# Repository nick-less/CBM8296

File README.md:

The files I used to repair my Commodore 8296, maybe someone finds this useful. 
Its not my own work I just combined the XC9536 PLA from http://www.nightfallcrew.com/18/11/2009/xilink-cpld-xc9536-replacement-pla-for-commodore-64/
with the Equations from http://www.zimmers.net/anonftp/pub/cbm/firmware/computers/pet/8296/index.html

This is how it looks

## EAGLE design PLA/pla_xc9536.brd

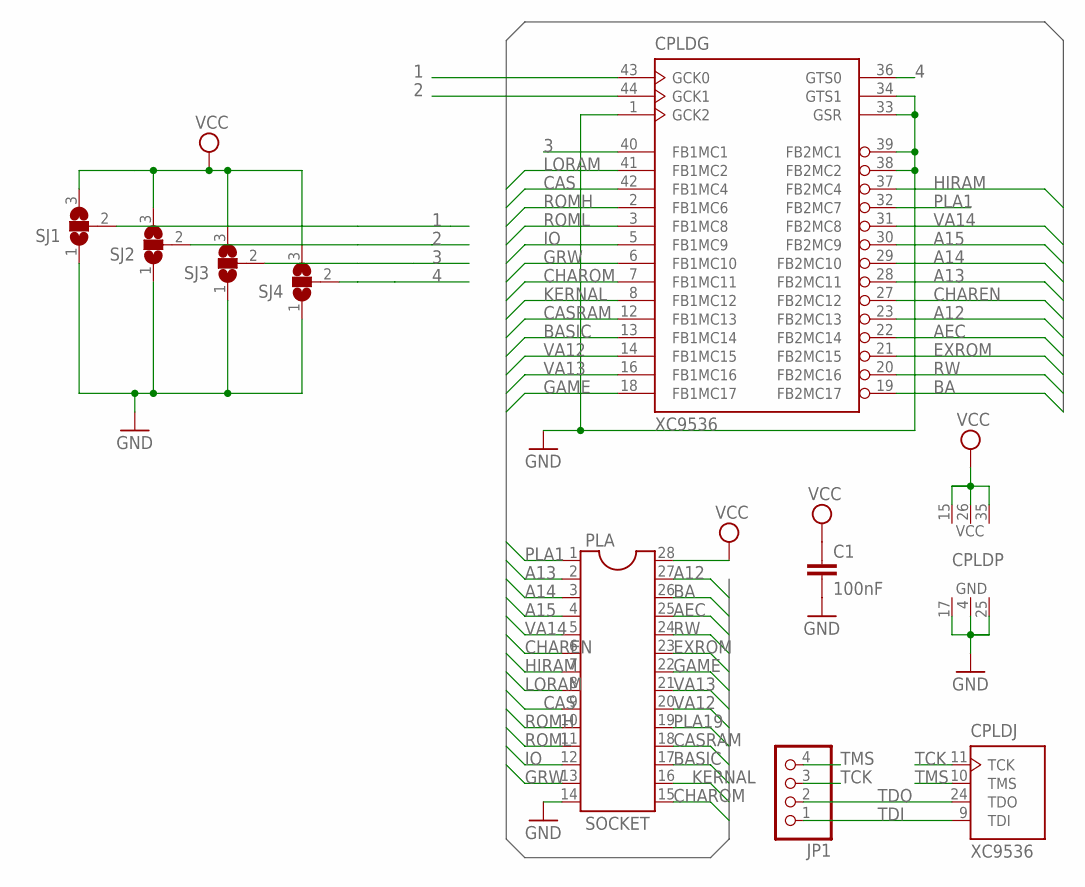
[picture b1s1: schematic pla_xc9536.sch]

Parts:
C1: 100nF; C1206K
CPLD: XC9536; VQ44
JP1: PINHD-1X4; 1X04
PLA: SOCKET; DIL28-6-ROUND
SJ1, SJ2, SJ3, SJ4: SJ2W; SJ_2

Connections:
1: CPLD.43 (GCK0), SJ1.2
2: CPLD.44 (GCK1), SJ2.2
3: CPLD.40 (FB1MC1), SJ3.2
4: CPLD.36 (GTS0), SJ4.2
A12: CPLD.23 (FB2MC13), PLA.27
A13: CPLD.28 (FB2MC11), PLA.2
A14: CPLD.29 (FB2MC10), PLA.3
A15: CPLD.30 (FB2MC9), PLA.4
AEC: CPLD.22 (FB2MC14), PLA.25
BA: CPLD.19 (FB2MC17), PLA.26
BASIC: CPLD.13 (FB1MC14), PLA.17
CAS: CPLD.42 (FB1MC4), PLA.9
CASRAM: CPLD.12 (FB1MC13), PLA.18
CHAREN: CPLD.27 (FB2MC12), PLA.6
CHAROM: CPLD.7 (FB1MC11), PLA.15
EXROM: CPLD.21 (FB2MC15), PLA.23
GAME: CPLD.18 (FB1MC17), PLA.22
GND: C1.2, CPLD.1 (GCK2), CPLD.4 (GND), CPLD.17 (GND), CPLD.25 (GND), CPLD.33 (GSR), CPLD.34 (GTS1), CPLD.38 (FB2MC2), CPLD.39 (FB2MC1), PLA.14, SJ1.1, SJ2.1, SJ3.1, SJ4.1
GRW: CPLD.6 (FB1MC10), PLA.13
HIRAM: CPLD.37 (FB2MC4), PLA.7
IO: CPLD.5 (FB1MC9), PLA.12
KERNAL: CPLD.8 (FB1MC12), PLA.16
LORAM: CPLD.41 (FB1MC2), PLA.8
PLA1: CPLD.32 (FB2MC7), PLA.1
PLA19: PLA.19
ROMH: CPLD.2 (FB1MC6), PLA.10
ROML: CPLD.3 (FB1MC8), PLA.11
RW: CPLD.20 (FB2MC16), PLA.24
TCK: CPLD.11 (TCK), JP1.3
TDI: CPLD.9 (TDI), JP1.1
TDO: CPLD.24 (TDO), JP1.2
TMS: CPLD.10 (TMS), JP1.4
VA12: CPLD.14 (FB1MC15), PLA.20
VA13: CPLD.16 (FB1MC16), PLA.21
VA14: CPLD.31 (FB2MC8), PLA.5
VCC: C1.1, CPLD.15 (VCC), CPLD.26 (VCC), CPLD.35 (VCC), PLA.28, SJ1.3, SJ2.3, SJ3.3, SJ4.3

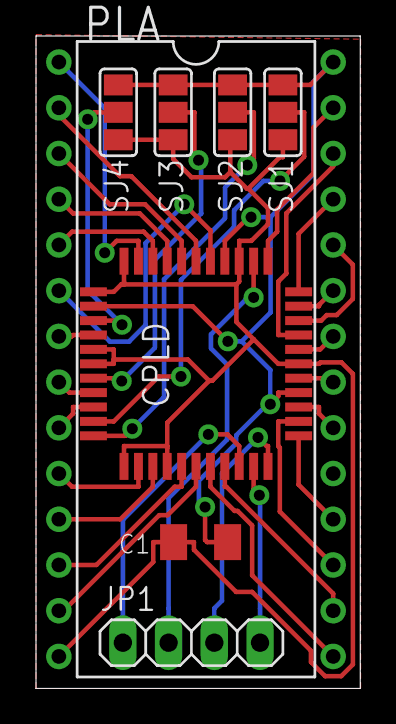
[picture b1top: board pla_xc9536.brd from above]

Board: 2 copper layers, 18.0 x 36.2 mm, 8 parts (0 on the bottom side), 35 nets.

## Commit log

2017-10-26 files used to create a working UC6 PLA for the 8296
2019-04-05 added a picture ;)
2019-04-05 bigger image
2019-11-28 updated schematic to remove floating pins
